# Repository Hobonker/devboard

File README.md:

# Devboard

# Inspiration 
I've never done such a large and complex custom PCB before, so I wanted to learn how to. The project helped me learn a lot about wiring and challenged me.
# What is it?
It's a custom PCB using an rp2040. Some other features are flash memory, USB-C power input, 12MHz crystal oscillator and a MCP1700 LDO voltage regulator.

# PCB
Here are some images of the board

# Bom
| Top Designator | Total Price ($) | Product Link |
|----------------|----------------|--------------|
| C1, C10 | 0.029 | https://jlcpcb.com/partdetail/53938-CL05A105KA5NQNC/C52923 |
| C8, C6, C5, C4, C2, C7, C11, C9, C12, C17, C3 | 0.0605 | https://jlcpcb.com/partdetail/1877-CL05B104KO5NNNC/C1525 |
| C13, C14 | 0.056 | https://jlcpcb.com/partdetail/20411-CL10A106KP8NNNC/C19702 |
| C16, C15 | 0.01 | https://jlcpcb.com/partdetail/1914-0402CG330J500NT/C1562 |
| J1 | 0.18 | https://jlcpcb.com/partdetail/Korean_HropartsElec-TYPE_C_31_M12/C165948 |
| J3, J2 | 0.14 | https://jlcpcb.com/partdetail/51993-2_54_1_20P/C50981 |
| J4 | 0.03 | https://jlcpcb.com/partdetail/25717-1_27_1_3P/C24980 |
| R2, R1 | 0.005 | https://jlcpcb.com/partdetail/26648-0402WGF5101TCE/C25905 |
| R3, R4 | 0.011 | https://jlcpcb.com/partdetail/25843-0402WGF270JTCE/C25100 |
| R6, R5 | 0.005 | https://jlcpcb.com/partdetail/12256-0402WGF1001TCE/C11702 |
| R7 | 0.0025 | https://jlcpcb.com/partdetail/26487-0402WGF1002TCE/C25744 |
| SW1 | 0.06 | https://jlcpcb.com/partdetail/XUNPU-TS_1088AR02016/C720477 |
| U1 | 0.98 | https://jlcpcb.com/partdetail/RaspberryPi-RP2040/C2040 |
| U2 | 0.49 | https://jlcpcb.com/partdetail/MicrochipTech-MCP1700T_3302ETT/C39051 |
| U4 | 0.71 | https://jlcpcb.com/partdetail/WinbondElec-W25Q16JVUXIQ/C2843335 |

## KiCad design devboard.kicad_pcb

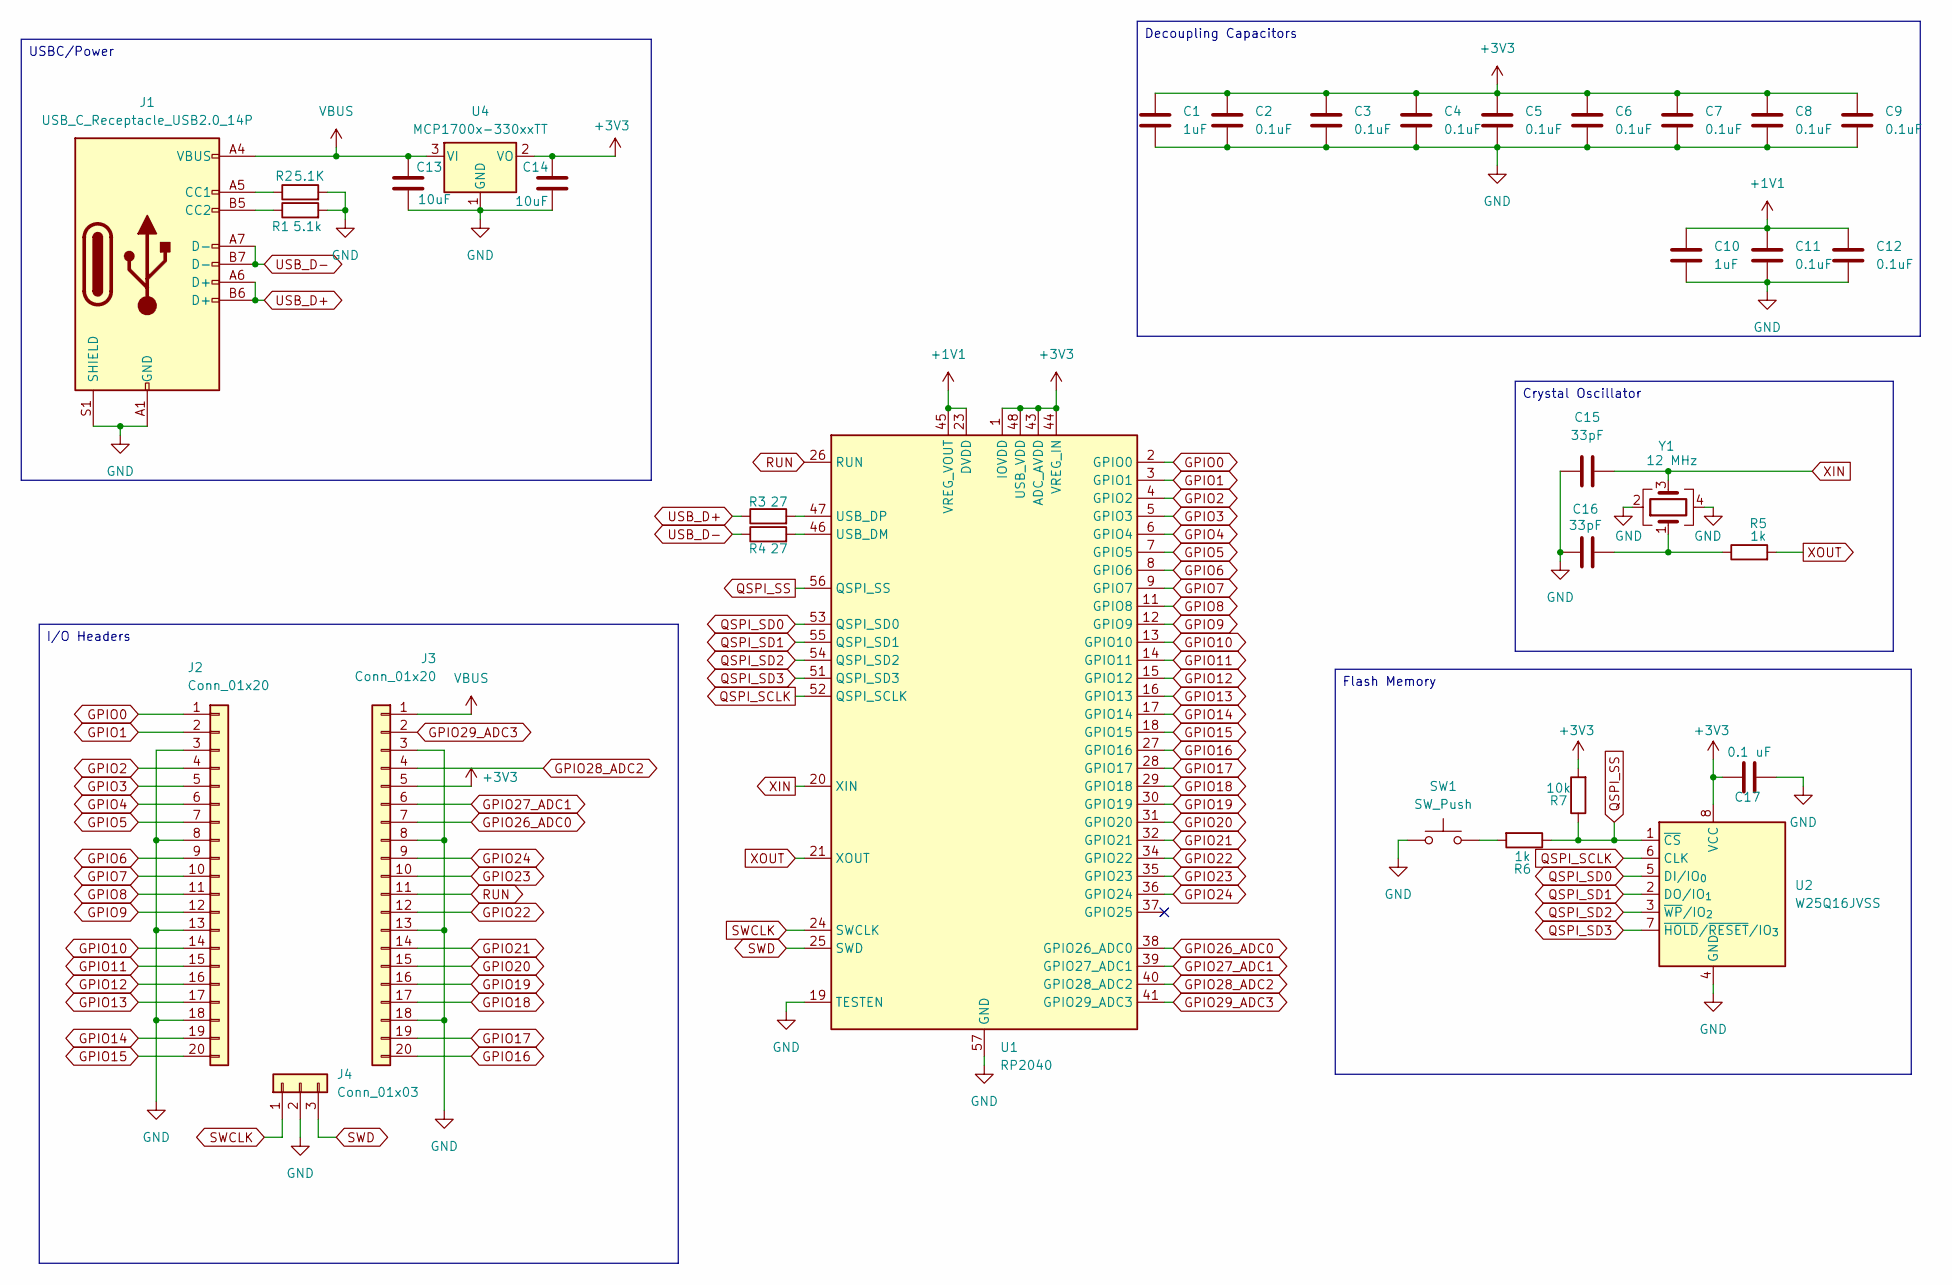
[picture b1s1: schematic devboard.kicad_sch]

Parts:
C1, C10: 1uF; C_0402_1005Metric
C2, C3, C4, C5, C6, C7, C8, C9, C11, C12: 0.1uF; C_0402_1005Metric
C13, C14: 10uF; C_0603_1608Metric
C15, C16: 33pF; C_0402_1005Metric
C17: 0.1 uF; C_0402_1005Metric
J1: USB_C_Receptacle_USB2.0_14P; USB_C_Receptacle_HRO_TYPE-C-31-M-12
J2, J3: Conn_01x20; PinHeader_1x20_P2.54mm_Vertical
J4: Conn_01x03; PinHeader_1x03_P2.54mm_Vertical
R1: 5.1k; R_0402_1005Metric
R2: 5.1K; R_0402_1005Metric
R3, R4: 27; R_0402_1005Metric
R5, R6: 1k; R_0402_1005Metric
R7: 10k; R_0402_1005Metric
SW1: SW_Push; SW_Push_SPST_NO_Alps_SKRK
U1: RP2040; QFN-56-1EP_7x7mm_P0.4mm_EP3.2x3.2mm
U2: W25Q16JVSS; Winbond_USON-8-1EP_3x2mm_P0.5mm_EP0.2x1.6mm
U4: MCP1700x-330xxTT; SOT-23
Y1: 12 MHz; Crystal_SMD_3225-4Pin_3.2x2.5mm

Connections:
+1V1: C10.1, C11.1, C12.1, U1.23 (DVDD), U1.45 (VREG_VOUT), U1.50 (DVDD)
+3V3: C1.1, C2.1, C3.1, C4.1, C5.1, C6.1, C7.1, C8.1, C9.1, C14.1, C17.1, J3.5, R7.2, U1.1 (IOVDD), U1.10 (IOVDD), U1.22 (IOVDD), U1.33 (IOVDD), U1.42 (IOVDD), U1.43 (ADC_AVDD), U1.44 (VREG_IN), U1.48 (USB_VDD), U1.49 (IOVDD), U2.8 (VCC), U4.2 (VO)
GND: C1.2, C2.2, C3.2, C4.2, C5.2, C6.2, C7.2, C8.2, C9.2, C10.2, C11.2, C12.2, C13.2, C14.2, C15.1, C16.1, C17.2, J1.A1 (GND), J1.A12 (GND), J1.B1 (GND), J1.B12 (GND), J1.S1 (SHIELD), J2.3, J2.8, J2.13, J2.18, J3.3, J3.8, J3.13, J3.18, J4.2, R1.2, R2.2, SW1.1, U1.19 (TESTEN), U1.57 (GND), U2.4 (GND), U4.1 (GND), Y1.2, Y1.4
GPIO0: J2.1, U1.2 (GPIO0)
GPIO1: J2.2, U1.3 (GPIO1)
GPIO2: J2.4, U1.4 (GPIO2)
GPIO3: J2.5, U1.5 (GPIO3)
GPIO4: J2.6, U1.6 (GPIO4)
GPIO5: J2.7, U1.7 (GPIO5)
GPIO6: J2.9, U1.8 (GPIO6)
GPIO7: J2.10, U1.9 (GPIO7)
GPIO8: J2.11, U1.11 (GPIO8)
GPIO9: J2.12, U1.12 (GPIO9)
GPIO10: J2.14, U1.13 (GPIO10)
GPIO11: J2.15, U1.14 (GPIO11)
GPIO12: J2.16, U1.15 (GPIO12)
GPIO13: J2.17, U1.16 (GPIO13)
GPIO14: J2.19, U1.17 (GPIO14)
GPIO15: J2.20, U1.18 (GPIO15)
GPIO16: J3.20, U1.27 (GPIO16)
GPIO17: J3.19, U1.28 (GPIO17)
GPIO18: J3.17, U1.29 (GPIO18)
GPIO19: J3.16, U1.30 (GPIO19)
GPIO20: J3.15, U1.31 (GPIO20)
GPIO21: J3.14, U1.32 (GPIO21)
GPIO22: J3.12, U1.34 (GPIO22)
GPIO23: J3.10, U1.35 (GPIO23)
GPIO24: J3.9, U1.36 (GPIO24)
GPIO26_ADC0: J3.7, U1.38 (GPIO26_ADC0)
GPIO27_ADC1: J3.6, U1.39 (GPIO27_ADC1)
GPIO28_ADC2: J3.4, U1.40 (GPIO28_ADC2)
GPIO29_ADC3: J3.2, U1.41 (GPIO29_ADC3)
unnamed: C16.2, R5.1, Y1.1
unnamed: J1.A5 (CC1), R2.1
unnamed: J1.B5 (CC2), R1.1
unnamed: R6.2, SW1.2
unnamed: R4.2, U1.46 (USB_DM)
unnamed: R3.2, U1.47 (USB_DP)
QSPI_SCLK: U1.52 (QSPI_SCLK), U2.6 (CLK)
QSPI_SD0: U1.53 (QSPI_SD0), U2.5 (DI/IO_{0})
QSPI_SD1: U1.55 (QSPI_SD1), U2.2 (DO/IO_{1})
QSPI_SD2: U1.54 (QSPI_SD2), U2.3 (~WP/IO_{2})
QSPI_SD3: U1.51 (QSPI_SD3), U2.7 (~HOLD/~RESET/IO_{3})
QSPI_SS: R6.1, R7.1, U1.56 (QSPI_SS), U2.1 (~CS)
RUN: J3.11, U1.26 (RUN)
SWCLK: J4.1, U1.24 (SWCLK)
SWD: J4.3, U1.25 (SWD)
USB_D+: J1.A6 (D+), J1.B6 (D+), R3.1
USB_D-: J1.A7 (D-), J1.B7 (D-), R4.1
VBUS: C13.1, J1.A4 (VBUS), J1.A9 (VBUS), J1.B4 (VBUS), J1.B9 (VBUS), J3.1, U4.3 (VI)
XIN: C15.2, U1.20 (XIN), Y1.3
XOUT: R5.2, U1.21 (XOUT)

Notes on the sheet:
Decoupling Capacitors
I/O Headers
Crystal Oscillator
USBC/Power
Flash Memory

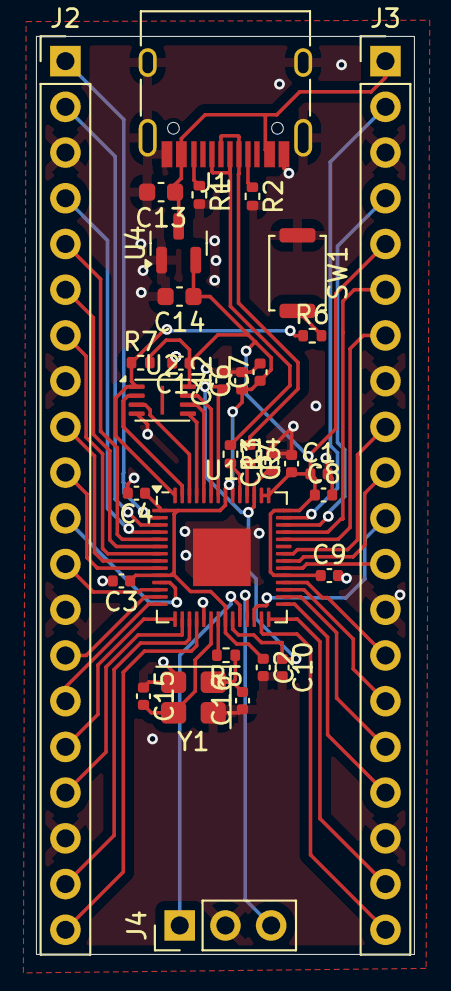
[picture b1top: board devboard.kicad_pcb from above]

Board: 2 copper layers, 21.0 x 51.0 mm, 33 parts (0 on the bottom side), 52 nets.

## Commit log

2026-05-04 Rename devboard.kicad_pcb to production/devboard.kicad_pcb
2026-05-04 Rename devboard.kicad_pro to production/devboard.kicad_pro
2026-05-04 Rename devboard.kicad_sch to production/devboard.kicad_sch
2026-05-04 Rename JOURNAL.md to README.md
2026-05-04 Rename README.md to journal.md
